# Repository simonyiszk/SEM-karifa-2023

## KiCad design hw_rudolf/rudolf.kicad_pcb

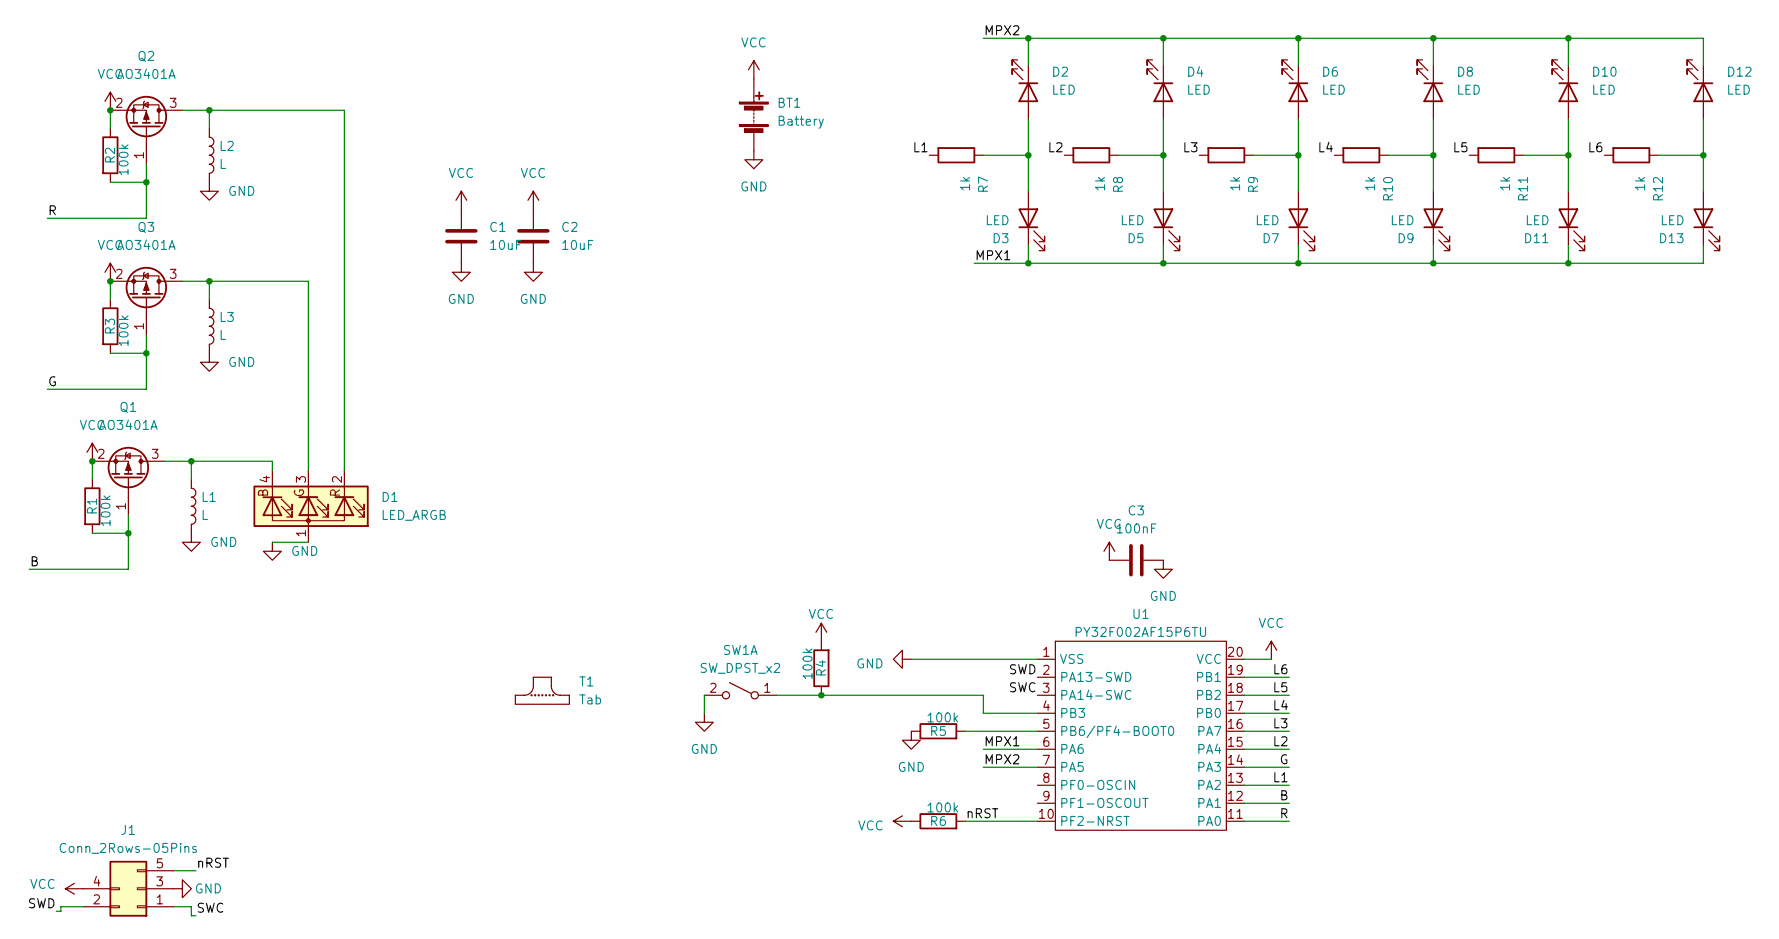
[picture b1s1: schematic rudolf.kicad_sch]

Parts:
BT1: Battery; CR2032_Holder
C1, C2: 10uF; C_0805_2012Metric
C3: 100nF; C_0805_2012Metric
D1: LED_ARGB; LED_RGB_Wuerth-PLCC4_3.2x2.8mm_150141M173100
D2, D3, D4, D5, D6, D7, D8, D9, D10, D11, D12, D13: LED; LED_0805_2012Metric
J1: Conn_2Rows-05Pins; ProgConnector_5pin
L1, L2, L3: L; L_Ferrocore_DLG-0403
Q1, Q2, Q3: AO3401A; SOT-23
R1, R2, R3, R4, R5, R6: 100k; R_0603_1608Metric
R7, R8, R9, R10, R11, R12: 1k; R_0603_1608Metric
SW1: SW_DPST_x2; SW_SPST_TL3342
T1: Tab
U1: PY32F002AF15P6TU; TSSOP-20_4.4x6.5mm_P0.65mm

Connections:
/B: Q1.1 (G), R1.2, U1.12 (PA1)
/G: Q3.1 (G), R3.2, U1.14 (PA3)
/L1: R7.2, U1.13 (PA2)
/L2: R8.2, U1.15 (PA4)
/L3: R9.2, U1.16 (PA7)
/L4: R10.2, U1.17 (PB0)
/L5: R11.2, U1.18 (PB2)
/L6: R12.2, U1.19 (PB1)
/MPX1: D3.1 (K), D5.1 (K), D7.1 (K), D9.1 (K), D11.1 (K), D13.1 (K), U1.6 (PA6)
/MPX2: D2.1 (K), D4.1 (K), D6.1 (K), D8.1 (K), D10.1 (K), D12.1 (K), U1.7 (PA5)
/R: Q2.1 (G), R2.2, U1.11 (PA0)
/SWC: J1.1, U1.3 (PA14-SWC)
/SWD: J1.2, U1.2 (PA13-SWD)
/nRST: J1.5, R6.2, U1.10 (PF2-NRST)
GND: BT1.2 (-), C1.2, C2.2, C3.1, D1.1 (A), J1.3, L1.2, L2.2, L3.2, R5.1, SW1.2 (B), U1.1 (VSS)
unnamed: D1.4 (BK), L1.1, Q1.3 (D)
unnamed: D1.3 (GK), L3.1, Q3.3 (D)
unnamed: D1.2 (RK), L2.1, Q2.3 (D)
unnamed: D2.2 (A), D3.2 (A), R7.1
unnamed: D4.2 (A), D5.2 (A), R8.1
unnamed: D6.2 (A), D7.2 (A), R9.1
unnamed: D8.2 (A), D9.2 (A), R10.1
unnamed: D10.2 (A), D11.2 (A), R11.1
unnamed: D12.2 (A), D13.2 (A), R12.1
unnamed: R4.1, SW1.1 (A), U1.4 (PB3)
unnamed: R5.2, U1.5 (PB6/PF4-BOOT0)
VCC: BT1.1 (+), C1.1, C2.1, C3.2, J1.4, Q1.2 (S), Q2.2 (S), Q3.2 (S), R1.1, R2.1, R3.1, R4.2, R6.1, U1.20 (VCC)

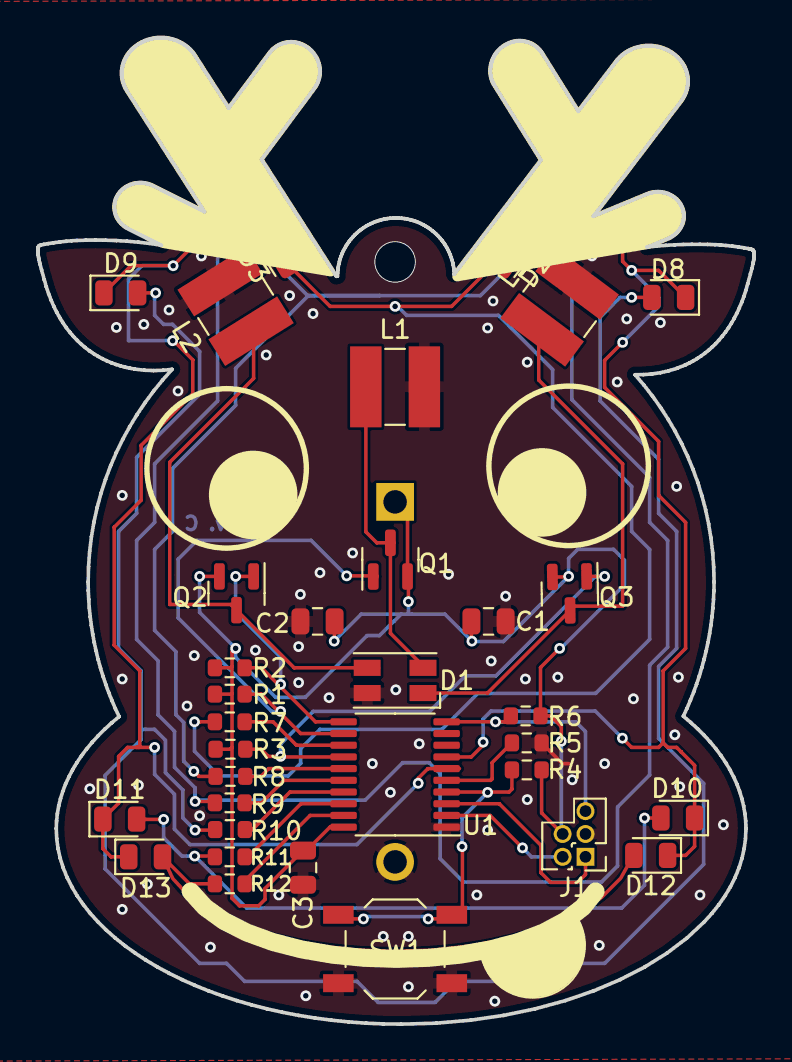
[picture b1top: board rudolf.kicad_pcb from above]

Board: 2 copper layers, 39.8 x 54.8 mm, 41 parts (1 on the bottom side), 27 nets.

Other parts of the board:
T1#2, T1#3: Tab

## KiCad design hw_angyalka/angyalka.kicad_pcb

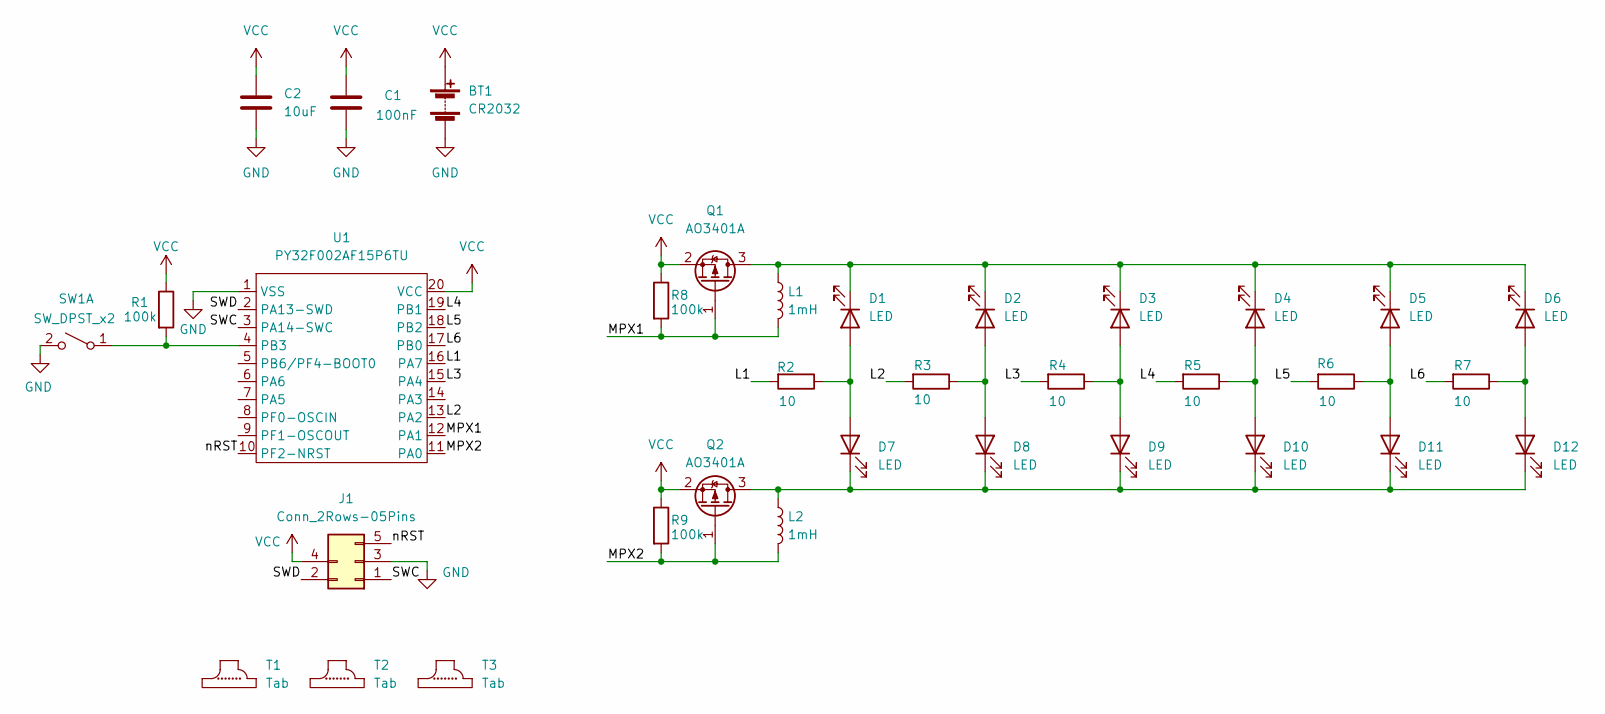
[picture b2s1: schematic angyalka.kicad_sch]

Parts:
BT1: CR2032; CR2032_Holder
C1: 100nF; C_0805_2012Metric
C2: 10uF; C_0805_2012Metric
D1, D2, D3, D4, D5, D6, D7, D8, D9, D10, D11, D12: LED; LED_0805_2012Metric
J1: Conn_2Rows-05Pins; ProgConnector_5pin
L1, L2: 1mH; L_Ferrocore_DLG-0403
Q1, Q2: AO3401A; SOT-23
R1, R8, R9: 100k; R_0603_1608Metric
R2, R3, R4, R5, R6, R7: 10; R_0603_1608Metric
SW1: SW_DPST_x2; SW_SPST_TL3342
T1, T2, T3: Tab
U1: PY32F002AF15P6TU; TSSOP-20_4.4x6.5mm_P0.65mm

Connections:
/L1: R2.2, U1.16 (PA7)
/L2: R3.2, U1.13 (PA2)
/L3: R4.2, U1.15 (PA4)
/L4: R5.2, U1.19 (PB1)
/L5: R6.2, U1.18 (PB2)
/L6: R7.2, U1.17 (PB0)
/MPX1: L1.2, Q1.1 (G), R8.2, U1.12 (PA1)
/MPX2: L2.2, Q2.1 (G), R9.2, U1.11 (PA0)
/SWC: J1.1, U1.3 (PA14-SWC)
/SWD: J1.2, U1.2 (PA13-SWD)
/nRST: J1.5, U1.10 (PF2-NRST)
GND: BT1.2 (-), C1.2, C2.2, J1.3, SW1.2 (B), U1.1 (VSS)
unnamed: D1.2 (A), D7.2 (A), R2.1
unnamed: D1.1 (K), D2.1 (K), D3.1 (K), D4.1 (K), D5.1 (K), D6.1 (K), L1.1, Q1.3 (D)
unnamed: D2.2 (A), D8.2 (A), R3.1
unnamed: D3.2 (A), D9.2 (A), R4.1
unnamed: D4.2 (A), D10.2 (A), R5.1
unnamed: D7.1 (K), D8.1 (K), D9.1 (K), D10.1 (K), D11.1 (K), D12.1 (K), L2.1, Q2.3 (D)
unnamed: D5.2 (A), D11.2 (A), R6.1
unnamed: D6.2 (A), D12.2 (A), R7.1
unnamed: R1.2, SW1.1 (A), U1.4 (PB3)
VCC: BT1.1 (+), C1.1, C2.1, J1.4, Q1.2 (S), Q2.2 (S), R1.1, R8.1, R9.1, U1.20 (VCC)

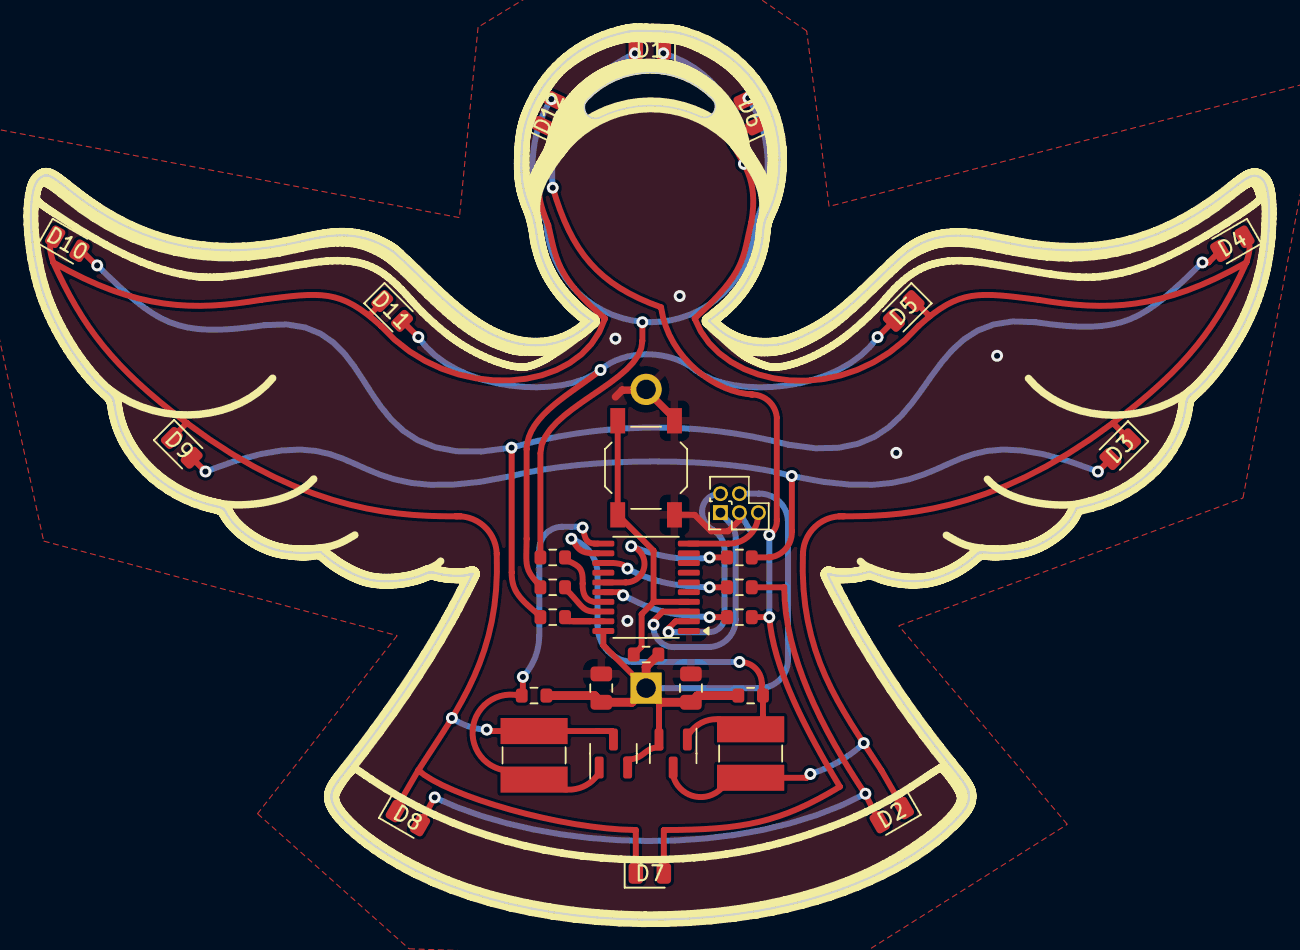
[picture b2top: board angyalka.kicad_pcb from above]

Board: 2 copper layers, 82.9 x 59.5 mm, 34 parts (1 on the bottom side), 22 nets.

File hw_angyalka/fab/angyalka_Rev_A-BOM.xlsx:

Comment | Designator | Footprint | JLCPCB Part #（optional）
PY32F002AF15P6TU | U1 | TSSOP-20 | C5292059
1mH | L1, L2 | 4.5x4 | C41408560
AO3401A | Q1, Q2 | SOT-23 | C15127
100k | R1, R8, R9 | 0603 | C25803
White LED | D1, D2, D3, D4, D5, D6, D7, D8, D9, D10, D11, D12 | 0805 | C34499
10 | R2, R3, R4, R5, R6, R7 | 0603 | C22859
SW_DPST_x2 | SW1 | SMD | C318884
10uF | C2 | 0805 | C15850
100nF | C1 | 0805 | C49678

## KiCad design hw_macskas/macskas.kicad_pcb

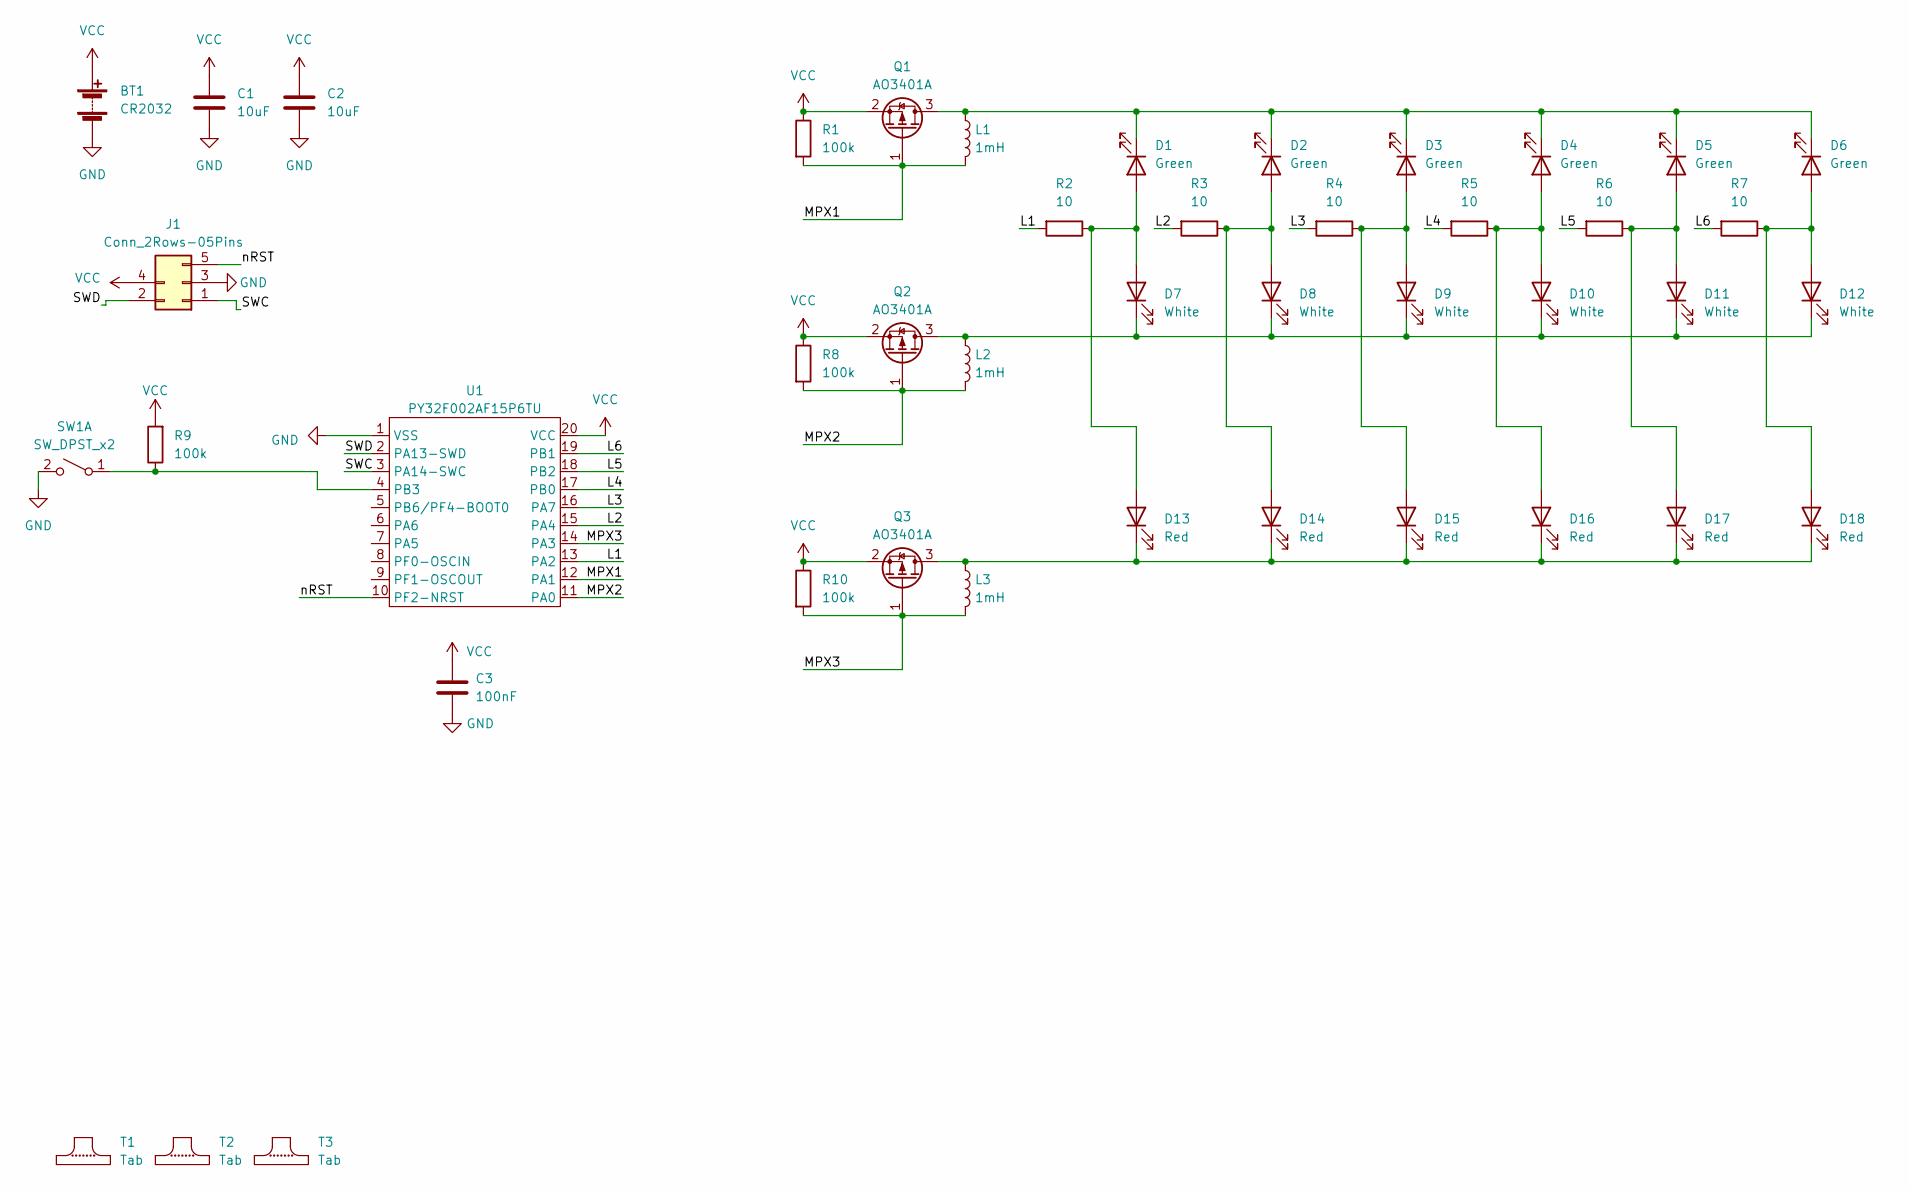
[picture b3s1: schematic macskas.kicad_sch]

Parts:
BT1: CR2032; CR2032_Holder
C1, C2: 10uF; C_0805_2012Metric
C3: 100nF; C_0805_2012Metric
D1, D2, D3, D4, D5, D6: Green; LED_0805_2012Metric
D7, D8, D9, D10, D11, D12: White; LED_0805_2012Metric
D13, D14, D15, D16, D17, D18: Red; LED_0805_2012Metric
J1: Conn_2Rows-05Pins; ProgConnector_5pin
L1, L2, L3: 1mH; L_Ferrocore_DLG-0403
Q1, Q2, Q3: AO3401A; SOT-23
R1, R8, R9, R10: 100k; R_0603_1608Metric
R2, R3, R4, R5, R6, R7: 10; R_0603_1608Metric
SW1: SW_DPST_x2; SW_SPST_TL3342
T1, T2, T3: Tab
U1: PY32F002AF15P6TU; TSSOP-20_4.4x6.5mm_P0.65mm

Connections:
/L1: R2.2, U1.13 (PA2)
/L2: R3.2, U1.15 (PA4)
/L3: R4.2, U1.16 (PA7)
/L4: R5.2, U1.17 (PB0)
/L5: R6.2, U1.18 (PB2)
/L6: R7.2, U1.19 (PB1)
/MPX1: L1.2, Q1.1 (G), R1.2, U1.12 (PA1)
/MPX2: L2.2, Q2.1 (G), R8.2, U1.11 (PA0)
/MPX3: L3.2, Q3.1 (G), R10.2, U1.14 (PA3)
/SWC: J1.1, U1.3 (PA14-SWC)
/SWD: J1.2, U1.2 (PA13-SWD)
/nRST: J1.5, U1.10 (PF2-NRST)
GND: BT1.2 (-), C1.2, C2.2, C3.1, J1.3, SW1.2 (B), U1.1 (VSS)
unnamed: D1.2 (A), D7.2 (A), D13.2 (A), R2.1
unnamed: D1.1 (K), D2.1 (K), D3.1 (K), D4.1 (K), D5.1 (K), D6.1 (K), L1.1, Q1.3 (D)
unnamed: D4.2 (A), D10.2 (A), D16.2 (A), R5.1
unnamed: D7.1 (K), D8.1 (K), D9.1 (K), D10.1 (K), D11.1 (K), D12.1 (K), L2.1, Q2.3 (D)
unnamed: D5.2 (A), D11.2 (A), D17.2 (A), R6.1
unnamed: D6.2 (A), D12.2 (A), D18.2 (A), R7.1
unnamed: D13.1 (K), D14.1 (K), D15.1 (K), D16.1 (K), D17.1 (K), D18.1 (K), L3.1, Q3.3 (D)
unnamed: D2.2 (A), D8.2 (A), D14.2 (A), R3.1
unnamed: D3.2 (A), D9.2 (A), D15.2 (A), R4.1
unnamed: R9.1, SW1.1 (A), U1.4 (PB3)
VCC: BT1.1 (+), C1.1, C2.1, C3.2, J1.4, Q1.2 (S), Q2.2 (S), Q3.2 (S), R1.1, R8.1, R9.2, R10.1, U1.20 (VCC)

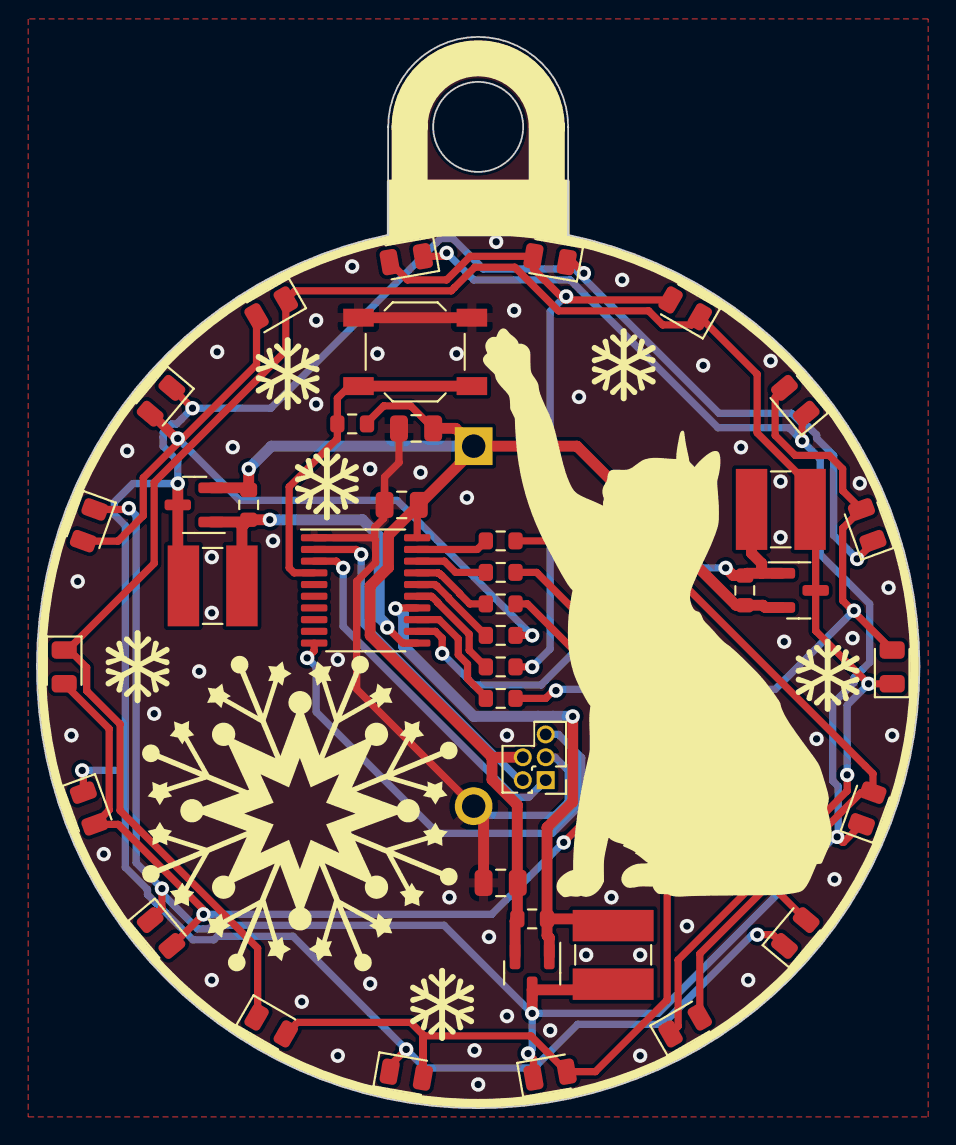
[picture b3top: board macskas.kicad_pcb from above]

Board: 2 copper layers, 49.0 x 59.5 mm, 44 parts (1 on the bottom side), 24 nets.

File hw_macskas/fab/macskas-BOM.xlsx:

Comment | Designator | Footprint | JLCPCB Part #（optional）
PY32F002AF15P6TU | U1 | TSSOP-20 | C5292059
1mH | L1, L2, L3 | SMD,4.5x4mm | C41408560
AO3401A | Q1, Q2, Q3 | SOT-23 | C15127
100k | R1, R8, R9, R10 | 0603 | C25803
Green LED | D1, D2, D3, D4, D5, D6 | 0805 | C2297
White LED | D7, D8, D9, D10, D11, D12 | 0805 | C34499
Red LED | D13, D14, D15, D16, D17, D18 | 0805 | C84256
10 | R2, R3, R4, R5, R6, R7 | 0603 | C22859
SW_DPST_x2 | SW1 | SMD | C318884
10uF | C1, C2 | 0805 | C15850
100nF | C3 | 0805 | C49678

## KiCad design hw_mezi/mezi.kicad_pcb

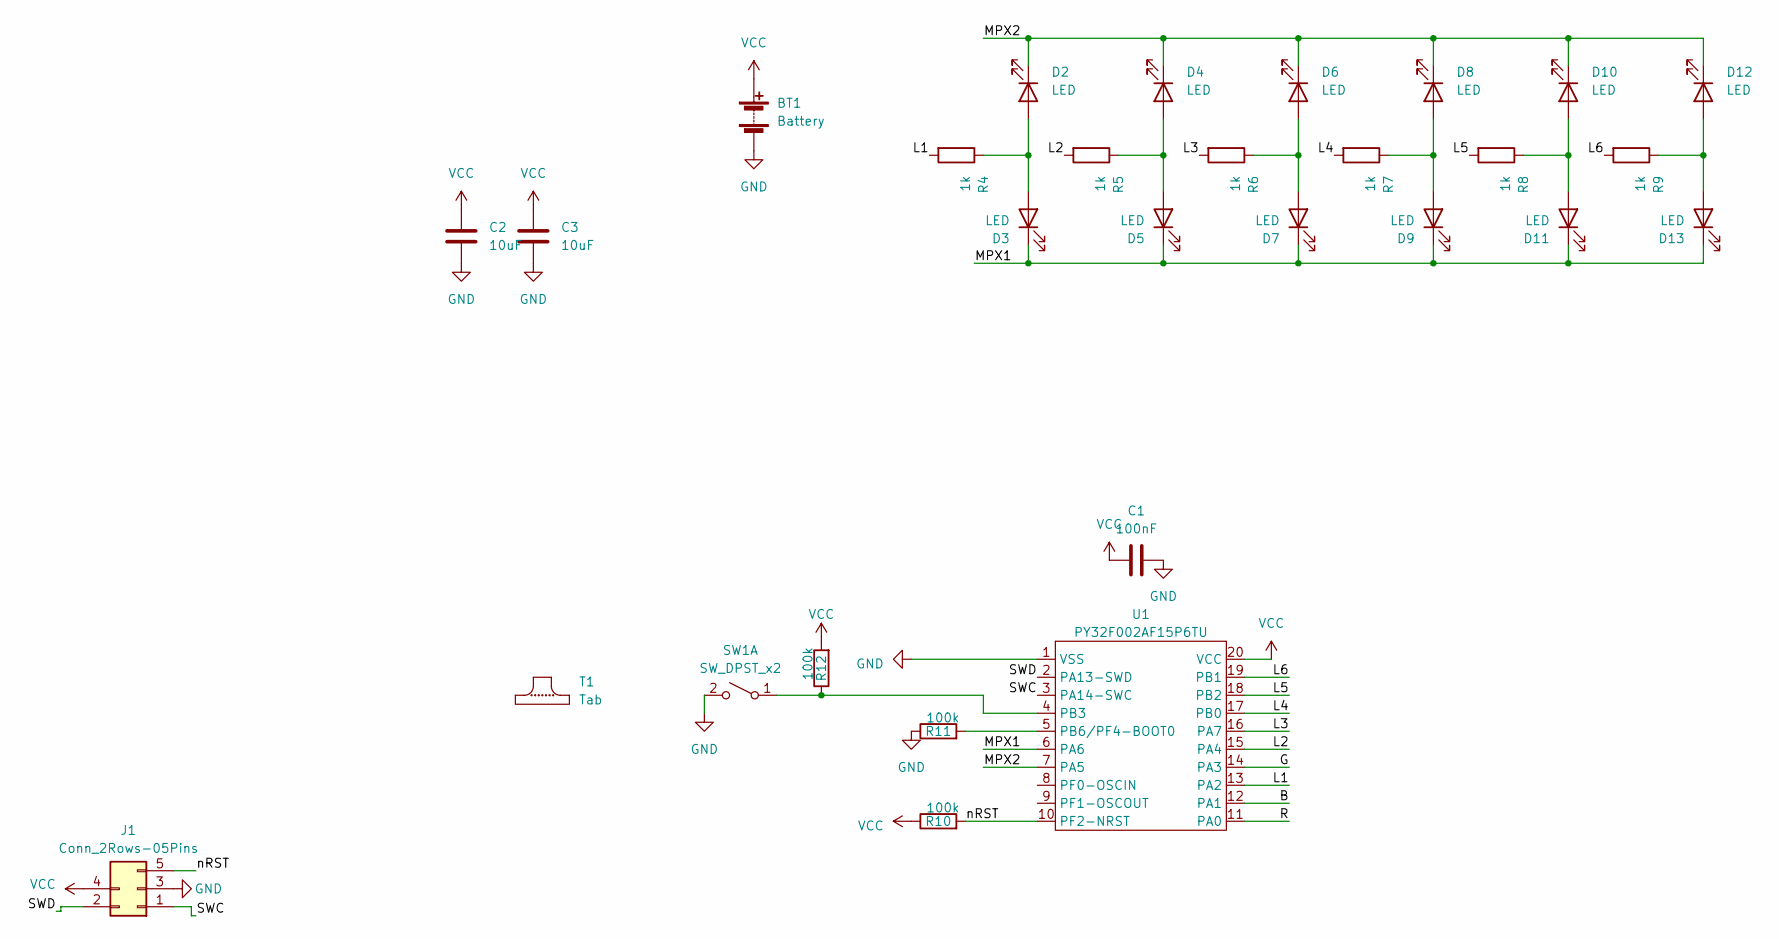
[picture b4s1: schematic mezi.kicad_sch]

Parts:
BT1: Battery; CR2032_Holder
C1: 100nF; C_0805_2012Metric
C2, C3: 10uF; C_0805_2012Metric
D2, D3, D4, D5, D6, D7, D8, D9, D10, D11, D12, D13: LED; LED_0805_2012Metric
J1: Conn_2Rows-05Pins; ProgConnector_5pin
R4, R5, R6, R7, R8, R9: 1k; R_0603_1608Metric
R10, R11, R12: 100k; R_0603_1608Metric
SW1: SW_DPST_x2; SW_SPST_TL3342
T1: Tab
U1: PY32F002AF15P6TU; TSSOP-20_4.4x6.5mm_P0.65mm

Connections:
/B: U1.12 (PA1)
/G: U1.14 (PA3)
/L1: R4.2, U1.13 (PA2)
/L2: R5.2, U1.15 (PA4)
/L3: R6.2, U1.16 (PA7)
/L4: R7.2, U1.17 (PB0)
/L5: R8.2, U1.18 (PB2)
/L6: R9.2, U1.19 (PB1)
/MPX1: D3.1 (K), D5.1 (K), D7.1 (K), D9.1 (K), D11.1 (K), D13.1 (K), U1.6 (PA6)
/MPX2: D2.1 (K), D4.1 (K), D6.1 (K), D8.1 (K), D10.1 (K), D12.1 (K), U1.7 (PA5)
/R: U1.11 (PA0)
/SWC: J1.1, U1.3 (PA14-SWC)
/SWD: J1.2, U1.2 (PA13-SWD)
/nRST: J1.5, R10.2, U1.10 (PF2-NRST)
GND: BT1.2 (-), C1.1, C2.2, C3.2, J1.3, R11.1, SW1.2 (B), U1.1 (VSS)
unnamed: D2.2 (A), D3.2 (A), R4.1
unnamed: D4.2 (A), D5.2 (A), R5.1
unnamed: D6.2 (A), D7.2 (A), R6.1
unnamed: D8.2 (A), D9.2 (A), R7.1
unnamed: D10.2 (A), D11.2 (A), R8.1
unnamed: D12.2 (A), D13.2 (A), R9.1
unnamed: R12.1, SW1.1 (A), U1.4 (PB3)
unnamed: R11.2, U1.5 (PB6/PF4-BOOT0)
VCC: BT1.1 (+), C1.2, C2.1, C3.1, J1.4, R10.1, R12.2, U1.20 (VCC)

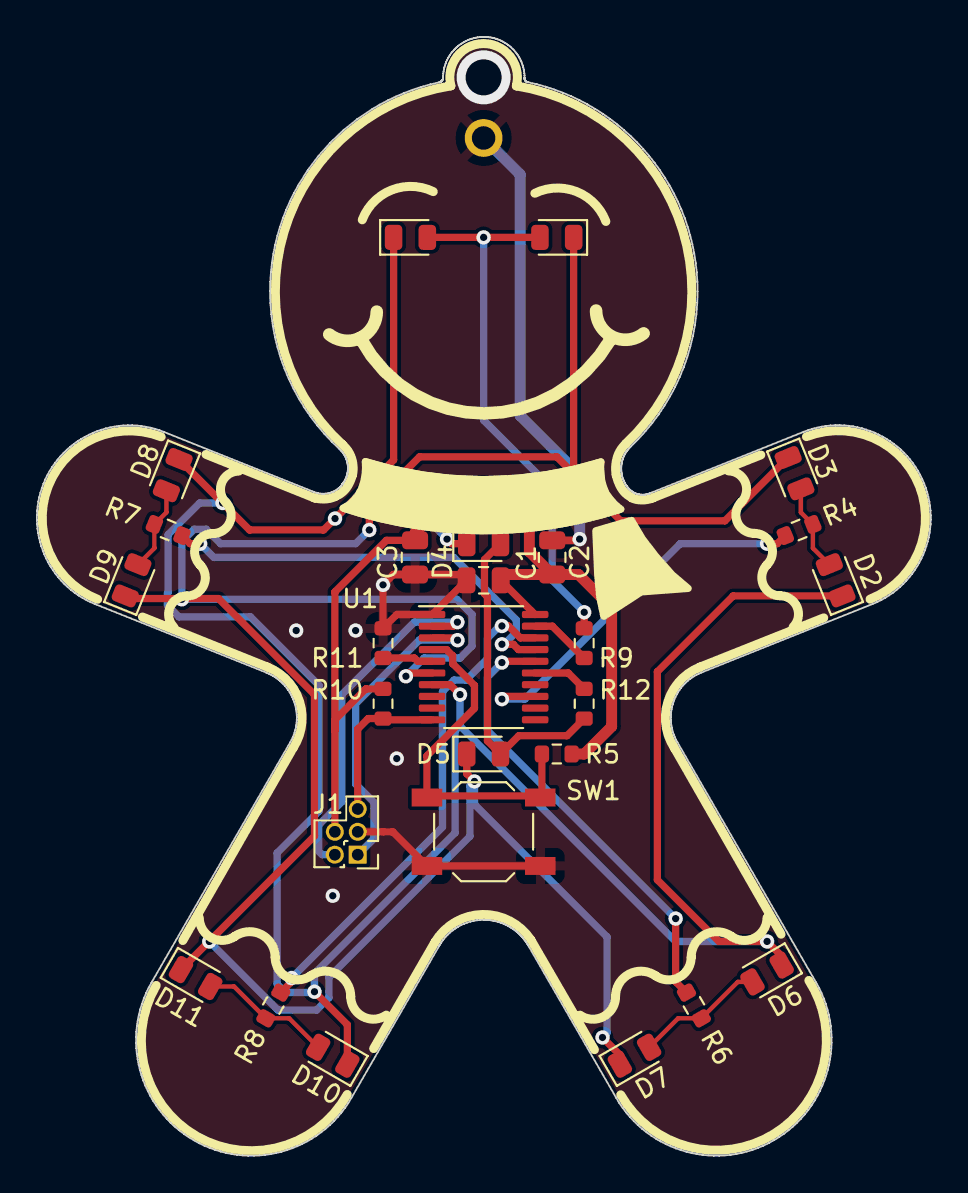
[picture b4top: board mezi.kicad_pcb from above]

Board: 2 copper layers, 49.7 x 62.2 mm, 32 parts (1 on the bottom side), 21 nets.

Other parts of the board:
T1#2, T1#3, T53,086: Tab

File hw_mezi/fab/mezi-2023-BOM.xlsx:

Comment | Designator | Footprint | JLCPCB Part #（optional）
PY32F002AF15P6TU | U1 | TSSOP-20 | C5292059
100k | R10, R11, R12 | 0603 | C25803
Yellow LED | D2, D3, D4, D5, D6, D7, D8, D9, D10, D11, D12, D13 | 0805 | C2296
1k | R4, R5, R6, R7, R8, R9 | 0603 | C21190
SW_DPST_x2 | SW1 | SMD | C318884
10uF | C2, C3 | 0805 | C15850
100nF | C1 | 0805 | C49678

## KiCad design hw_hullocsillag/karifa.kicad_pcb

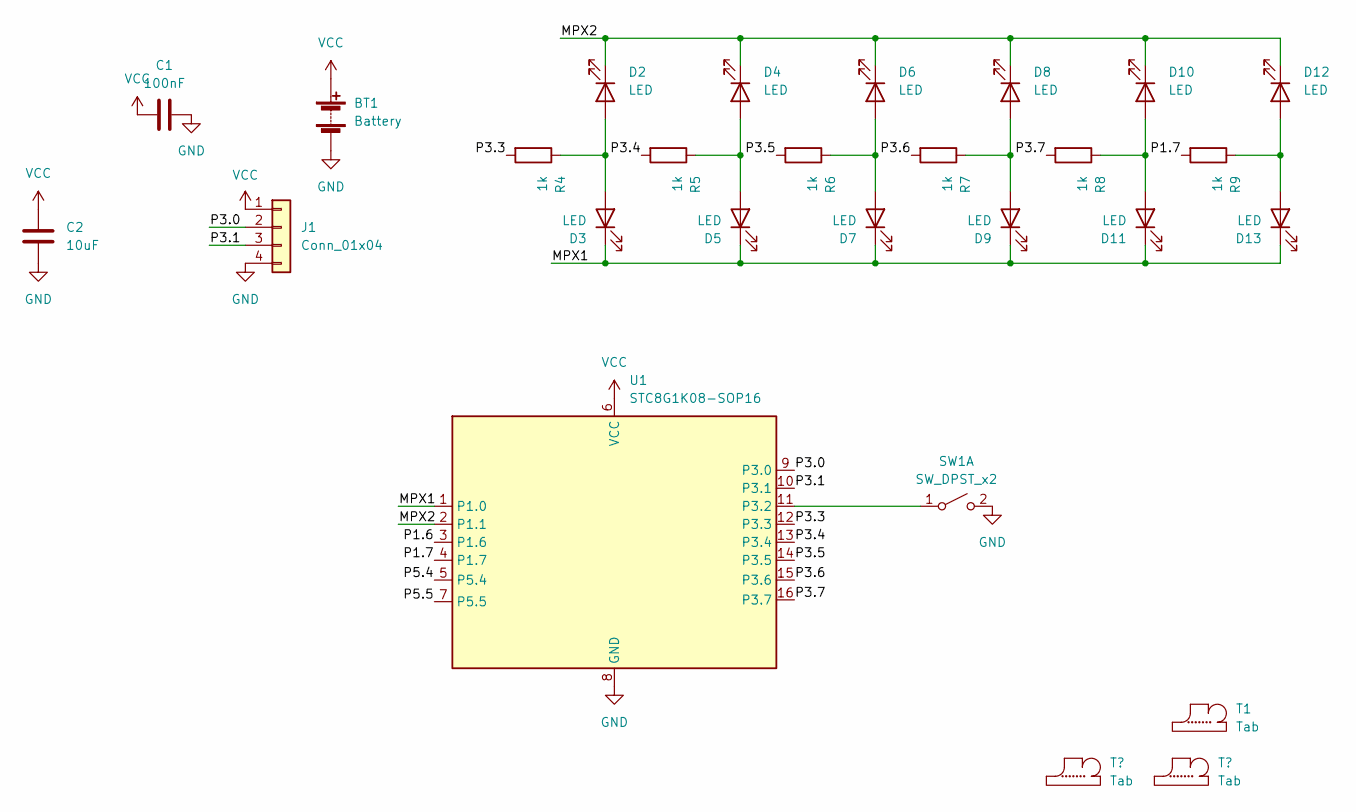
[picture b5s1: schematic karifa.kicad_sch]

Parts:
BT1: Battery; CR2032_Holder
C1: 100nF; C_0805_2012Metric
C2: 10uF; C_0805_2012Metric
D2, D3, D4, D5, D6, D7, D8, D9, D10, D11, D12, D13: LED; LED_0805_2012Metric
J1: Conn_01x04; PinHeader_1x04_P1.27mm_Vertical
R4, R5, R6, R7, R8, R9: 1k; R_0603_1608Metric
SW1: SW_DPST_x2; SW_Push_K2-1102SP
T1: Tab
U1: STC8G1K08-SOP16; STC_SOP-16_3.9x9.9mm_P1.27mm

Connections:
/MPX1: D3.1 (K), D5.1 (K), D7.1 (K), D9.1 (K), D11.1 (K), D13.1 (K), U1.1 (P1.0)
/MPX2: D2.1 (K), D4.1 (K), D6.1 (K), D8.1 (K), D10.1 (K), D12.1 (K), U1.2 (P1.1)
/P1.6: U1.3 (P1.6)
/P1.7: R9.2, U1.4 (P1.7)
/P3.0: J1.2, U1.9 (P3.0)
/P3.1: J1.3, U1.10 (P3.1)
/P3.3: R4.2, U1.12 (P3.3)
/P3.4: R5.2, U1.13 (P3.4)
/P3.5: R6.2, U1.14 (P3.5)
/P3.6: R7.2, U1.15 (P3.6)
/P3.7: R8.2, U1.16 (P3.7)
/P5.4: U1.5 (P5.4)
/P5.5: U1.7 (P5.5)
GND: BT1.2 (-), C1.1, C2.2, J1.4, SW1.2 (B), U1.8 (GND)
unnamed: D2.2 (A), D3.2 (A), R4.1
unnamed: D4.2 (A), D5.2 (A), R5.1
unnamed: D6.2 (A), D7.2 (A), R6.1
unnamed: D8.2 (A), D9.2 (A), R7.1
unnamed: D10.2 (A), D11.2 (A), R8.1
unnamed: D12.2 (A), D13.2 (A), R9.1
unnamed: SW1.1 (A), U1.11 (P3.2)
VCC: BT1.1 (+), C1.2, C2.1, J1.1, U1.6 (VCC)

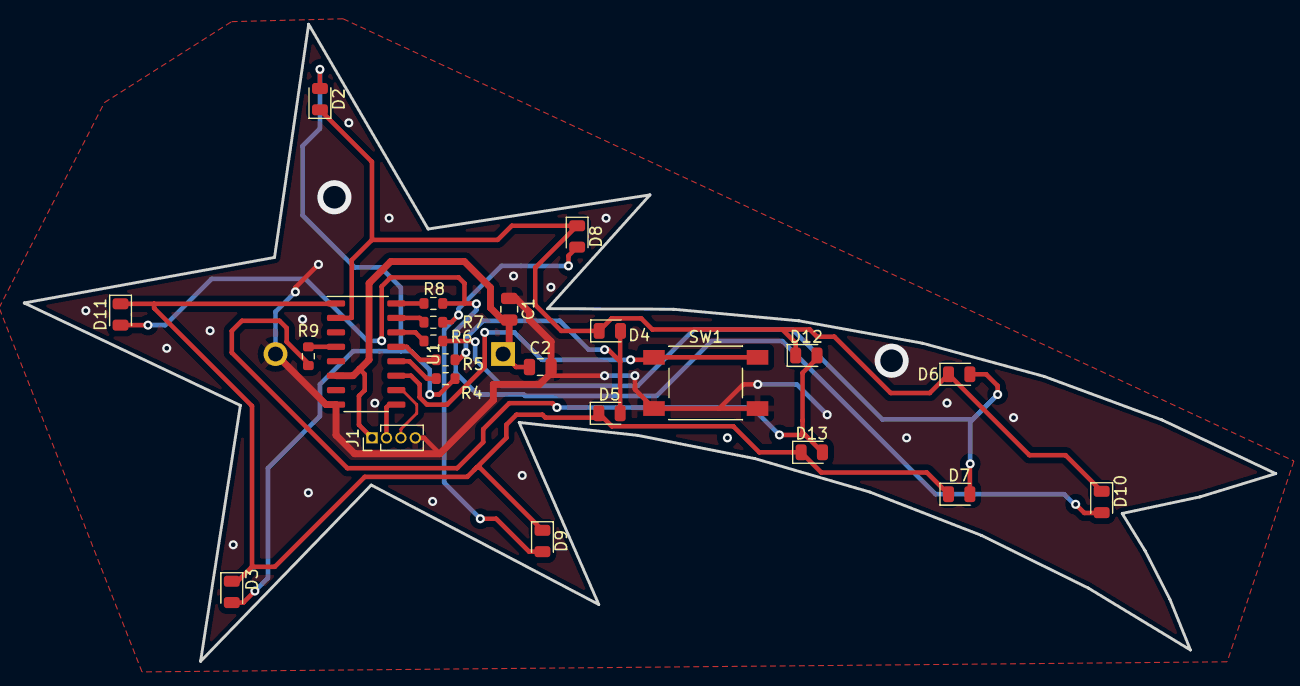
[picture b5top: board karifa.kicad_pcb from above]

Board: 2 copper layers, 110.0 x 56.0 mm, 27 parts (1 on the bottom side), 19 nets.

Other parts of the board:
T2, T3: Tab

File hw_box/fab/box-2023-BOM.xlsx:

Comment | Designator | Footprint | JLCPCB Part #（optional）
PY32F002AF15P6TU | U1 | TSSOP-20 | C5292059
100k | R10, R11, R12 | 0603 | C25803
Yellow LED | D2, D3, D4, D5, D6, D7, D8, D9, D10, D11, D12, D13 | 0805 | C2296
1k | R4, R5, R6, R7, R8, R9 | 0603 | C21190
SW_DPST_x2 | SW1 | SMD | C318884
10uF | C2, C3 | 0805 | C15850
100nF | C1 | 0805 | C49678

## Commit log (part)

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2023-11-07 Initial commit.
2023-11-09 Added Christmas tree PCB.
2023-11-12 Generalized gitignore + fixed SOT-23 reference
2023-11-12 Fixed TSSOP references
2023-11-12 Added hoember - no tracks yet
2023-11-12 Added shape SVGs
2023-11-12 Added hopehely project
2023-11-12 Added mezi project
2023-11-17 Hópehely routed.
2023-11-18 Hoember + Mezi routed
2023-11-19 Fixed remenyo's overwrite error.
2023-11-19 Fixed silkscreen.
2023-11-20 Footprint fix for JLCPCB assembly.
2023-11-20 Can be manufactured.
2023-11-20 Hópehely panelized.
2023-11-20 mezi tssop JLC swap + hole on top
2023-11-20 Added hoember and mezi panel
2023-11-20 Added fabrication files for hoember and mezi.
2023-11-25 Ported battery level measurement to PY32.
2023-11-26 Saves persistent data to the last flash sector.
2023-11-26 Button access + year updates.
2023-11-26 Fixed flash erase.
2023-11-28 This should work on the real hardware.
2023-11-29 Added configuration and fixed power-down mode.
2023-11-29 Fixed power-down animation.
2023-12-03 Added new animations for new shapes + retrofitted a few of the existing ones
2023-12-03 LEDs and battery level for hopehely.
2023-12-03 Fixed animations so they compile.
2023-12-04 Hopehely animations.
2023-12-04 Mezi animations.
2023-12-04 Mezi battery level.
2023-12-04 Fixed battery level on all PCBs.
2023-12-04 Fixed hoember animations.
2023-12-05 Added release binaries and flash loader ELF.
2024-11-23 Added animations for "Ajándékdoboz" and "Rudolf" figures.
2024-11-23 Added Ajándékdoboz and Rudolf hardware design files.
2024-12-02 Add animations for "Rudolf"
2024-12-04 Added final animations for "ajandekdoboz".
2025-07-13 Added macskas fadisz.
2025-08-30 Added boost converter driver.
2025-09-14 Branching from karifa-2023 to 2025-dev, add older hw_hullocsillag to repo.
2025-09-14 Added Hullocsillag
2025-09-16 Hullocsillag updated, new led driver
2025-09-23 Hullocsillag routed, C2 capacitor relocated, silkscreen added.
2025-09-29 Added switching current generator based LED driver and hullocsillag animations.
2025-09-30 Switching LED driver works.
2025-09-30 Working on cat design.
2025-10-01 Updated cat.
2025-10-01 Inductor updated, pull-up resistor added, filling reworked
2025-10-10 Macskas routed.
2025-10-10 Panelized.
2025-10-18 Sent to fab.
2025-10-19 Added Angyalka
2025-10-24 First Iteration
2025-10-24 box Rev.B
    modified the F. Mask, and rotate the Led4 and Led12
2025-10-24 Karifa silkscreen redesigned.
2025-10-24 Covered F.Mask around soldering pads
2025-10-24 Karifa updated and panelized.
2025-10-24 Angyalka panelized.
2025-10-24 mezi design update
2025-10-24 Gerber for Ajándékcsomag
2025-10-24 Hullocsillag silkscreen updated
2025-10-24 Hullocsillag gerbers generated.
2025-10-28 Updated for macskas hw.
2025-10-28 Added validity test for persistent data.
2025-10-28 Added some test animations and fixed the order of LEDs.
2025-10-28 Added battery level measurement for macskas.
2025-10-30 Added automatic animation program change.
2025-10-30 Change software timers to 32-bit.
2025-10-30 Moved timer base initialization from RGB LED driver to normal LED driver.
2025-10-30 Bugfix for 32-bit software timers.
2025-11-02 Update pcb
    Made FMask for exclude leds, added generated image
2025-11-03 Fixed switching LED driver.
2025-11-03 Increased brightness, added macskas animations.
2025-11-05 Fixed switching LED driver, so LEDs will have the same current flowing through them.
2025-11-06 Soldering guide.
2025-11-08 Added some files needed for manufacturing. Also fixed macskas Fab layer.
2025-11-21 New release binaries.
2025-11-26 Fixed LED resistors.
2025-11-26 Fixed order of LEDs.
2025-11-26 Updated value fields.
2025-12-01 Added hullocsillag and angyal animations and fw release.
